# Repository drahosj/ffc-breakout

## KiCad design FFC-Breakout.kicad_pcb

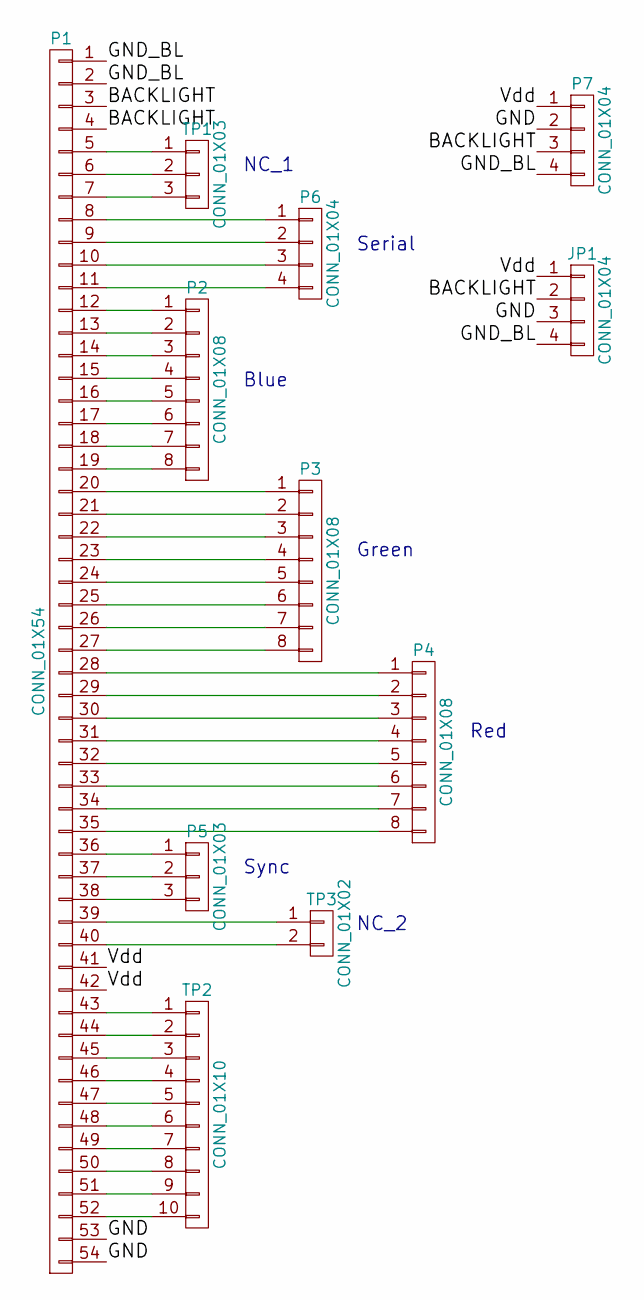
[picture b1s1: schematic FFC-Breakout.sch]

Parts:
JP1: CONN_01X04; Pin_Header_Straight_1x04_Pitch2.54mm
P1: CONN_01X54; Molex_FFC-51296-5494
P2, P3, P4: CONN_01X08; Pin_Header_Straight_1x08_Pitch2.54mm
P5: CONN_01X03; Pin_Header_Straight_1x03_Pitch2.54mm
P6, P7: CONN_01X04; Pin_Header_Straight_1x04_Pitch2.54mm
TP1: CONN_01X03; Pin_Header_Straight_1x03_Pitch2.54mm
TP2: CONN_01X10; Pin_Header_Straight_2x05_Pitch2.54mm
TP3: CONN_01X02; Pin_Header_Straight_1x02_Pitch2.54mm

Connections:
/BACKLIGHT: JP1.2, P1.3, P1.4, P7.3
/GND: JP1.3, P1.53, P1.54, P7.2
/GND_BL: JP1.4, P1.1, P1.2, P7.4
/Vdd: JP1.1, P1.41, P1.42, P7.1
unnamed: P1.5, TP1.1
unnamed: P1.6, TP1.2
unnamed: P1.7, TP1.3
unnamed: P1.8, P6.1
unnamed: P1.9, P6.2
unnamed: P1.10, P6.3
unnamed: P1.11, P6.4
unnamed: P1.12, P2.1
unnamed: P1.13, P2.2
unnamed: P1.14, P2.3
unnamed: P1.15, P2.4
unnamed: P1.16, P2.5
unnamed: P1.17, P2.6
unnamed: P1.18, P2.7
unnamed: P1.19, P2.8
unnamed: P1.20, P3.1
unnamed: P1.21, P3.2
unnamed: P1.22, P3.3
unnamed: P1.23, P3.4
unnamed: P1.24, P3.5
unnamed: P1.25, P3.6
unnamed: P1.26, P3.7
unnamed: P1.27, P3.8
unnamed: P1.28, P4.1
unnamed: P1.29, P4.2
unnamed: P1.30, P4.3
unnamed: P1.31, P4.4
unnamed: P1.32, P4.5
unnamed: P1.33, P4.6
unnamed: P1.34, P4.7
unnamed: P1.35, P4.8
unnamed: P1.36, P5.1
unnamed: P1.37, P5.2
unnamed: P1.38, P5.3
unnamed: P1.39, TP3.1
unnamed: P1.40, TP3.2
unnamed: P1.43, TP2.1
unnamed: P1.44, TP2.2
unnamed: P1.45, TP2.3
unnamed: P1.46, TP2.4
unnamed: P1.47, TP2.5
unnamed: P1.48, TP2.6
unnamed: P1.49, TP2.7
unnamed: P1.50, TP2.8
unnamed: P1.51, TP2.9
unnamed: P1.52, TP2.10

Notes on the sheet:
NC_1
Serial
Blue
Green
Red
Sync
NC_2

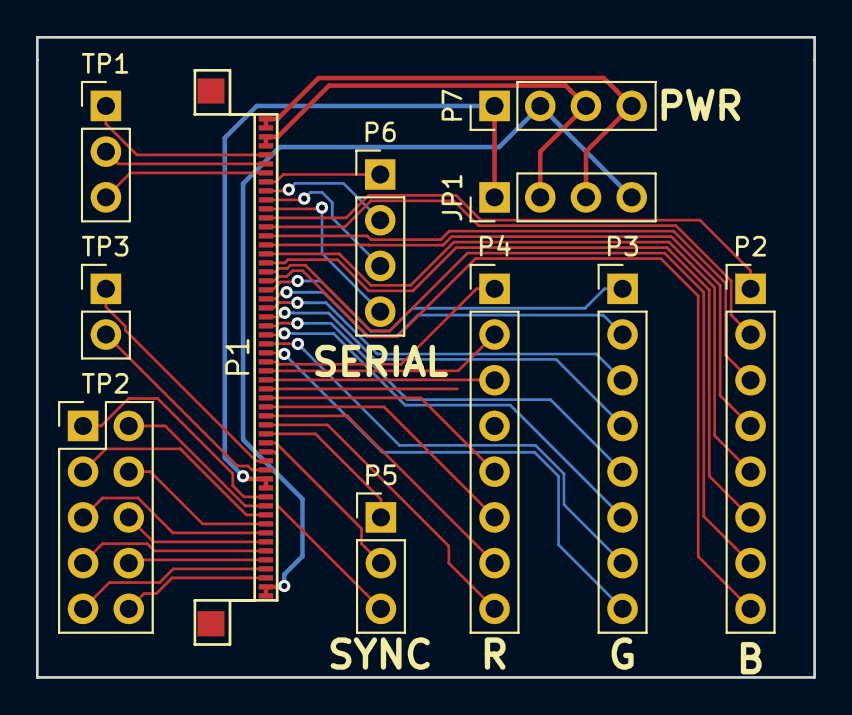
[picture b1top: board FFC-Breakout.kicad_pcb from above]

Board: 2 copper layers, 43.2 x 35.6 mm, 11 parts (0 on the bottom side), 50 nets.

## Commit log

2017-08-17 Initial commit
    It's basically done.
